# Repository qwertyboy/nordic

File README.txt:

This is a repository for various breakouts and development boards for Nordic Semiconductor RF devices. Utilized devices so far are the nRF24LU1+ and nRF24LO1.

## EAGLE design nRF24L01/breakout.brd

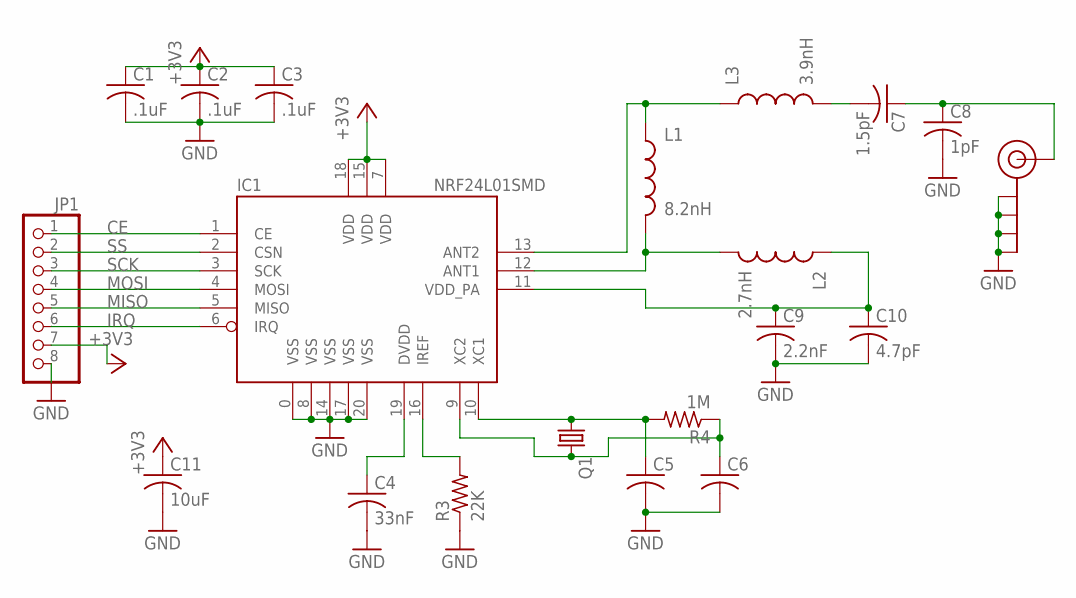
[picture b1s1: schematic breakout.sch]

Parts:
C1, C2, C3: .1uF; C0402
C4: 33nF; C0402
C5, C6: C-USC0402; C0402
C7: 1.5pF; C0402
C8: 1pF; C0402
C9: 2.2nF; C0402
C10: 4.7pF; C0402
C11: 10uF; C0805K
IC1: NRF24L01SMD; QFN20
J$1: SMA_EDGE; SMA-EDGE
JP1: PINHD-1X8; 1X08
L1: 8.2nH; C0402
L2: 2.7nH; C0402
L3: 3.9nH; C0402
Q1: CRYSTALHC49U-V; HC49U-V
R3: 22K; R0402
R4: 1M; R0402

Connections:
+3V3: C1.1, C2.1, C3.1, C11.1, IC1.7 (VDD), IC1.15 (VDD), IC1.18 (VDD), JP1.7
CE: IC1.1 (CE), JP1.1
GND: C1.2, C2.2, C3.2, C4.2, C5.2, C6.2, C8.2, C9.2, C10.2, C11.2, IC1.0 (VSS), IC1.8 (VSS), IC1.14 (VSS), IC1.17 (VSS), IC1.20 (VSS), J$1.GND@0 (GND), J$1.GND@1 (GND), J$1.GND@2 (GND), J$1.GND@3 (GND), JP1.8, R3.1
IRQ: IC1.6 (IRQ), JP1.6
MISO: IC1.5 (MISO), JP1.5
MOSI: IC1.4 (MOSI), JP1.4
unnamed: C4.1, IC1.19 (DVDD)
unnamed: IC1.16 (IREF), R3.2
unnamed: C5.1, IC1.10 (XC1), Q1.1, R4.2
unnamed: C6.1, IC1.9 (XC2), Q1.2, R4.1
unnamed: IC1.13 (ANT2), L1.1, L3.1
unnamed: IC1.12 (ANT1), L1.2, L2.2
unnamed: C7.2, L3.2
unnamed: C7.1, C8.1, J$1.SIG (SIGNAL)
unnamed: C9.1, C10.1, IC1.11 (VDD_PA), L2.1
SCK: IC1.3 (SCK), JP1.3
SS: IC1.2 (CSN), JP1.2

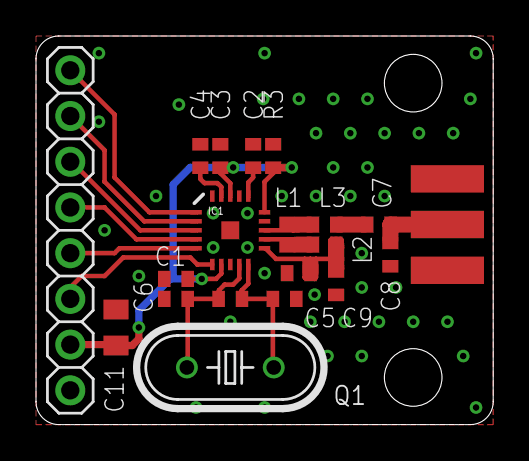
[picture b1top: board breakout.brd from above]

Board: 2 copper layers, 25.4 x 21.6 mm, 20 parts (0 on the bottom side), 17 nets.

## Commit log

2012-05-25 First commit. Added files for nRF24LU1+ USB breakout board.
2012-05-25 Renamed folder
2012-05-25 Fixing things
2012-05-25 Removed backup files
2012-05-25 Finished schematic
2012-05-25 Started board layout
2012-12-08 Added a basic breakout board for the 24L01
2013-06-26 cleaning up, added a revised usb breakout
